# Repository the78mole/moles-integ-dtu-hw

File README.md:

# Moles Integration DTU Hardware

This is a specialized integration module that combines an ESP32 microcontroller with a sub-GHz transceiver, primarily designed as a hardware foundation for [AhoyDTU](https://github.com/lumapu/ahoy/) and [OpenDTU](https://github.com/tbnobody/OpenDTU) solar inverter monitoring systems.

## Table of Contents

- [Features](#features)
- [Hardware Specifications](#hardware-specifications)
- [Hardware Assembly](#hardware-assembly)
- [Pin Mapping](#pin-mapping)
- [Software Installation](#software-installation)
- [Configuration](#configuration)
- [Troubleshooting](#troubleshooting)
- [Performance Specifications](#performance-specifications)
- [Improvements](#improvements)
- [Contributing](#contributing)
- [License](#license)
- [Resources](#resources)

## Features

- **ESP32 Integration**: Full ESP32 development board compatibility
- **Sub-GHz Communication**: NRF24L01+ transceiver support for solar inverter communication
- **Compact Design**: Optimized PCB layout for minimal footprint
- **Open Source**: Full KiCad project files and documentation
- **DTU Ready**: Pre-configured for AhoyDTU and OpenDTU deployment
- **RF Performance**: Optimized RF design with optional PA+LNA enhancement
- **Easy Assembly**: Interactive BOM and detailed assembly instructions

## Hardware Specifications

### Core Components

| Component | Specification | Description |
|-----------|--------------|-------------|
| **Microcontroller** | ESP32-WROOM-32 | Dual-core Xtensa LX6, WiFi & Bluetooth |
| **RF Transceiver** | NRF24L01+ | 2.4GHz ISM band, up to 2Mbps |
| **Power Supply** | 3.3V/5V compatible | On-board voltage regulation |
| **Flash Memory** | 4-16MB (ESP32 internal) | Program and data storage, depending on chosen WROOM-Module |
| **RAM** | 520KB (ESP32 internal) | SRAM for program execution |

### Physical Specifications

- **PCB Dimensions**: ~70mm x 50mm (approximate)
- **Layer Count**: 2-layer PCB
- **Operating Temperature**: -40°C to +85°C
- **Power Consumption**: 
  - Active: ~160mA @ 3.3V
  - Deep Sleep: <10µA
  - WiFi TX: ~200mA peak

### Electrical Specifications

- **Input Voltage**: 3.3V - 5V DC
- **I/O Voltage**: 3.3V logic level
- **Current Rating**: Max 1A total
- **ESD Protection**: Integrated on critical pins

## Hardware Assembly

### Required Tools

- Soldering iron (temperature controlled, 350-400°C)
- Solder (60/40 or lead-free 0.6-0.8mm)
- Flux
- Tweezers
- Magnifying glass or microscope
- Multimeter
- Hot air station (optional, for SMD components)

### Bill of Materials

For a complete and up-to-date bill of materials, please refer to the [Interactive BOM](https://htmlpreview.github.io/?https://github.com/the78mole/moles-integ-dtu-hw/blob/main/docs/ibom.html) which provides:

- Complete component list with values and package sizes
- Component placement visualization
- Interactive component highlighting
- Supplier information and part numbers

### Assembly Instructions

1. **Preparation**
   - Download and print the [PCB documentation](docs/Moles-Integ-DTU-HW.pdf)
   - Gather all components per the BOM
   - Prepare your workspace with proper lighting and ventilation

2. **SMD Component Assembly**
   - Start with the smallest components (resistors, capacitors)
   - Use flux liberally for better solder flow
   - Work from inside-out to avoid shadowing larger components
   - Double-check component orientations, especially for ICs

3. **Through-Hole Components**
   - Install connectors and larger components
   - Ensure proper mechanical fit before soldering
   - Clean flux residue with isopropyl alcohol

4. **ESP32 Module Installation**
   - Align the ESP32-WROOM-32 module carefully
   - Solder all pads ensuring good electrical contact
   - Verify no shorts between adjacent pins

5. **NRF24L01+ Socket/Module**
   - Install either the socket for removable modules or solder the NRF24L01+ directly
   - Verify pin alignment matches the board silkscreen
   - Test continuity of critical connections (VCC, GND, SPI pins)

6. **Quality Control**
   - Visual inspection for solder bridges
   - Continuity testing of power rails
   - Check for correct component placement

### Assembly Verification

Before first power-up:

```bash
# Basic continuity checks
- VCC to GND: Should be open (high resistance)
- 3.3V rail continuity
- SPI bus connectivity (MOSI, MISO, SCK, CS)
- ESP32 programming pins accessibility
```

## Pin Mapping

### ESP32 to NRF24L01+ Connections

| ESP32 Pin | Function | NRF24L01+ Pin | Description |
|-----------|----------|---------------|-------------|
| GPIO18 | SPI_SCK | SCK | SPI Clock |
| GPIO23 | SPI_MOSI | MOSI | SPI Master Out |
| GPIO19 | SPI_MISO | MISO | SPI Master In |
| GPIO5 | SPI_CS | CSN | SPI Chip Select |
| GPIO4 | GPIO | CE | Chip Enable |
| GPIO2 | GPIO | IRQ | Interrupt Request |
| 3V3 | Power | VCC | 3.3V Power Supply |
| GND | Ground | GND | Ground |

### Additional GPIO Mapping

| ESP32 Pin | Function | Description |
|-----------|----------|-------------|
| GPIO0 | BOOT | Boot mode selection |
| GPIO2 | LED | Status LED (if populated) |
| EN | Reset | External reset input |
| GPIO1 | UART_TX | Serial transmit |
| GPIO3 | UART_RX | Serial receive |

## Software Installation

### Prerequisites

- **ESP-IDF**: Version 4.4+ or Arduino IDE with ESP32 support
- **PlatformIO**: Recommended for advanced development
- **Git**: For cloning repositories
- **USB-to-Serial Driver**: CP210x or CH340 depending on your board

### Installing OpenDTU

OpenDTU is the recommended firmware for this hardware platform.

1. **Clone the Repository**
   ```bash
   git clone https://github.com/tbnobody/OpenDTU.git
   cd OpenDTU
   ```

2. **Configure PlatformIO**
   ```bash
   # Install PlatformIO if not already installed
   pip install platformio
   
   # Build the project
   pio run -e generic_esp32
   ```

3. **Flash the Firmware**
   ```bash
   # Connect the board via USB
   # Put ESP32 in programming mode (hold BOOT, press RESET, release BOOT)
   pio run -e generic_esp32 -t upload
   ```

### Installing AhoyDTU

Alternative firmware option with different feature set.

1. **Clone and Build**
   ```bash
   git clone https://github.com/lumapu/ahoy.git
   cd ahoy
   pio run -e esp32-wroom32-devkit
   ```

2. **Configuration**
   - Edit `config.h` for your specific inverter setup
   - Configure WiFi credentials
   - Set up MQTT broker details

### First Boot Configuration

1. **WiFi Setup**
   - Connect to the ESP32 access point (typically "OpenDTU-XXXX")
   - Navigate to the web interface
   - Configure your WiFi network credentials

2. **Inverter Configuration**
   - Enter your inverter serial numbers
   - Configure communication parameters
   - Set up monitoring intervals

## Configuration

### Web Interface

After successful installation, access the web interface:

- **Default IP**: Check your router's DHCP table or use mDNS
- **Default URL**: `http://opendtu.local` or `http://[IP_ADDRESS]`
- **Default Credentials**: Usually no authentication required initially

### Key Configuration Parameters

```yaml
# WiFi Configuration
wifi:
  ssid: "YourNetworkName"
  password: "YourNetworkPassword"
  
# MQTT Configuration
mqtt:
  broker: "192.168.1.100"
  port: 1883
  topic_prefix: "solar"
  
# Inverter Configuration
inverters:
  - serial: 1234567890
    name: "Inverter 1"
    type: "HM-600"
```

### Performance Tuning

For optimal RF performance:

1. **Antenna Placement**
   - Keep antenna away from metal objects
   - Ensure clear line of sight to inverters
   - Consider external antenna for better range

2. **Power Management**
   - Configure deep sleep modes for battery operation
   - Optimize polling intervals
   - Use efficient data transmission protocols

## Troubleshooting

### Common Issues

#### No WiFi Connection
```bash
# Check if ESP32 is in AP mode
# Look for "OpenDTU-XXXX" or "AhoyDTU-XXXX" network
# Connect and configure via web interface
```

#### RF Communication Problems
1. **Check NRF24L01+ Module**
   - Verify power supply (3.3V)
   - Check SPI connections
   - Ensure proper antenna connection

2. **Inverter Communication**
   - Verify inverter serial numbers
   - Check RF channel configuration
   - Monitor signal strength indicators

#### Programming Issues
```bash
# Put ESP32 in programming mode
# Hold BOOT button while pressing RESET
# Release RESET, then release BOOT
# Attempt upload again
```

### Diagnostic Commands

```bash
# Monitor serial output
pio device monitor -b 115200

# Check memory usage
pio run -t size

# Clean build artifacts
pio run -t clean
```

### Debug Output

Enable debug logging in your firmware configuration:

```cpp
// In Arduino IDE or PlatformIO
#define DEBUG_LEVEL ARDUHAL_LOG_LEVEL_DEBUG
```

## Performance Specifications

### RF Performance

| Parameter | Typical Value | Maximum Value | Unit |
|-----------|---------------|---------------|------|
| **Transmit Power** | 0 | +4 | dBm |
| **Receive Sensitivity** | -85 | -90 | dBm |
| **Range (Line of Sight)** | 100 | 200 | meters |
| **Range (Indoor)** | 20 | 50 | meters |
| **Data Rate** | 250k | 2M | bps |

### Power Consumption

| Mode | Current | Duration | Notes |
|------|---------|----------|-------|
| **Active WiFi** | 160mA | Continuous | Normal operation |
| **RF TX Peak** | 200mA | <1ms | During transmission |
| **Light Sleep** | 15mA | Variable | WiFi maintained |
| **Deep Sleep** | <10µA | Hours | Wake on timer/GPIO |

### Environmental Specifications

- **Operating Temperature**: -40°C to +85°C
- **Storage Temperature**: -65°C to +125°C
- **Humidity**: 5% to 95% RH (non-condensing)
- **Altitude**: Up to 3000m above sea level

## Improvements

### Hardware Enhancements

#### PA+LNA RF Frontend

To significantly improve RF performance and range:

**Benefits:**
- Increased transmit power (+20dBm typical)
- Improved receiver sensitivity (-100dBm)
- Extended range (up to 1km line of sight)

**Implementation:**
1. **Hardware Modification**
   - Add RFX2401C or similar PA+LNA module
   - Modify RF trace routing
   - Add antenna switching control

2. **Parts Required**
   - RFX2401C PA+LNA module
   - Additional control GPIOs
   - Modified PCB or breakout board

3. **Assembly Guide**
   - Follow the detailed guide: [NRF24L01+PA+LNA Module Build](https://www.instructables.com/How-to-Build-Your-Own-NRF24L01palna-Module/)
   - Ensure proper shielding and ground plane
   - Test RF performance with spectrum analyzer

#### Alternative Power Options

1. **Battery Operation**
   - Add LiPo battery connector
   - Implement charging circuit
   - Power management optimization

2. **PoE Support**
   - Add IEEE 802.3af PoE module
   - Galvanic isolation
   - Surge protection

#### Future Hardware Revisions

- **USB-C Connector**: Modern connector standard
- **On-board Antenna**: Integrated PCB antenna option
- **Status LEDs**: Visual feedback for operation modes
- **External Antenna Connector**: U.FL or SMA connector
- **Environmental Sensors**: Temperature, humidity monitoring

### Software Enhancements

#### Advanced Features
- **OTA Updates**: Over-the-air firmware updates
- **Data Logging**: Local storage of historical data
- **Advanced Scheduling**: Complex polling schedules
- **Multi-Protocol Support**: Support for additional inverter protocols

#### Integration Options
- **Home Assistant**: Native integration
- **InfluxDB**: Time-series database support
- **Grafana**: Advanced visualization
- **Node-RED**: Visual programming interface

## Contributing

We welcome contributions to improve this project! Here's how you can help:

### Development Workflow

1. **Fork the Repository**
   ```bash
   git clone https://github.com/[your-username]/moles-integ-dtu-hw.git
   cd moles-integ-dtu-hw
   ```

2. **Create Feature Branch**
   ```bash
   git checkout -b feature/your-improvement
   ```

3. **Make Changes**
   - Follow KiCad design rules
   - Update documentation
   - Test thoroughly

4. **Submit Pull Request**
   - Provide clear description
   - Include test results
   - Reference related issues

### Design Guidelines

#### Hardware Design
- **KiCad Version**: Use latest stable version
- **Design Rules**: Follow IPC standards
- **Component Selection**: Prefer widely available parts
- **Documentation**: Update schematic and PCB documentation

#### Documentation
- **Markdown Format**: Use standard markdown
- **Images**: Optimize file sizes, use PNG/JPG
- **Links**: Verify all external links
- **Accuracy**: Test all instructions

### Bug Reports

When reporting bugs, please include:

- **Hardware Version**: PCB revision and component details
- **Software Version**: Firmware version and configuration
- **Environment**: Operating conditions and setup
- **Reproduction Steps**: Clear steps to reproduce the issue
- **Expected vs Actual**: What should happen vs what actually happens

### Feature Requests

For new features:

- **Use Case**: Describe the problem you're trying to solve
- **Proposed Solution**: Your suggested approach
- **Alternatives**: Other solutions you've considered
- **Impact**: Who would benefit from this feature

## License

This project is licensed under the [TAPR Open Hardware License](LICENSE). This means:

### You are free to:
- **Study** the design and understand how it works
- **Modify** the design for your own purposes
- **Distribute** copies of the design
- **Distribute** modified versions of the design

### Under the following conditions:
- **Attribution**: Credit the original designers
- **Share Alike**: Distribute modifications under the same license
- **Documentation**: Provide design files in open formats
- **Notice**: Include license notices in distributions

### Commercial Use
Commercial use is permitted under the TAPR OHL, but please review the full license terms for specific requirements regarding documentation and attribution.

## Resources

### Official Documentation
- **Schematics**: [PDF Documentation](docs/Moles-Integ-DTU-HW.pdf)
- **Interactive BOM**: [iBOM Tool](https://htmlpreview.github.io/?https://github.com/the78mole/moles-integ-dtu-hw/blob/main/docs/ibom.html)
- **Production Workflow**: [Automated Production Files](docs/PRODUCTION_WORKFLOW.md)
- **Versioning & CI/CD**: [Semantic Versioning and Workflows](docs/VERSIONING_AND_CI.md)
- **KiCad Files**: Complete project files in repository

### Related Projects
- **OpenDTU**: [Advanced DTU firmware](https://github.com/tbnobody/OpenDTU)
- **AhoyDTU**: [Alternative DTU firmware](https://github.com/lumapu/ahoy/)
- **ESP32 Documentation**: [Official ESP32 docs](https://docs.espressif.com/projects/esp-idf/en/latest/)
- **NRF24L01+**: [Datasheet and examples](https://www.nordicsemi.com/products/nrf24l01)

### Community Resources
- **Solar Inverter Monitoring**: [Community forums and guides](https://forum.fhem.de)
- **ESP32 Community**: [ESP32 developer resources](https://esp32.com/)
- **KiCad Community**: [PCB design resources](https://kicad.org/community/)

### Supplier Information
- **PCB Manufacturing**: Recommended suppliers for small batch production
- **Component Sourcing**: Parts availability and alternative components
- **Assembly Services**: Professional assembly options

### Development Tools
- **KiCad**: [Free PCB design software](https://kicad.org/)
- **PlatformIO**: [Advanced embedded development](https://platformio.org/)
- **ESP-IDF**: [ESP32 development framework](https://github.com/espressif/esp-idf)
- **Git**: [Version control system](https://git-scm.com/)

---

**Disclaimer**: This project involves working with electrical circuits and RF equipment. Always follow proper safety procedures and local regulations. The authors are not responsible for any damage or injury resulting from the use of this design.

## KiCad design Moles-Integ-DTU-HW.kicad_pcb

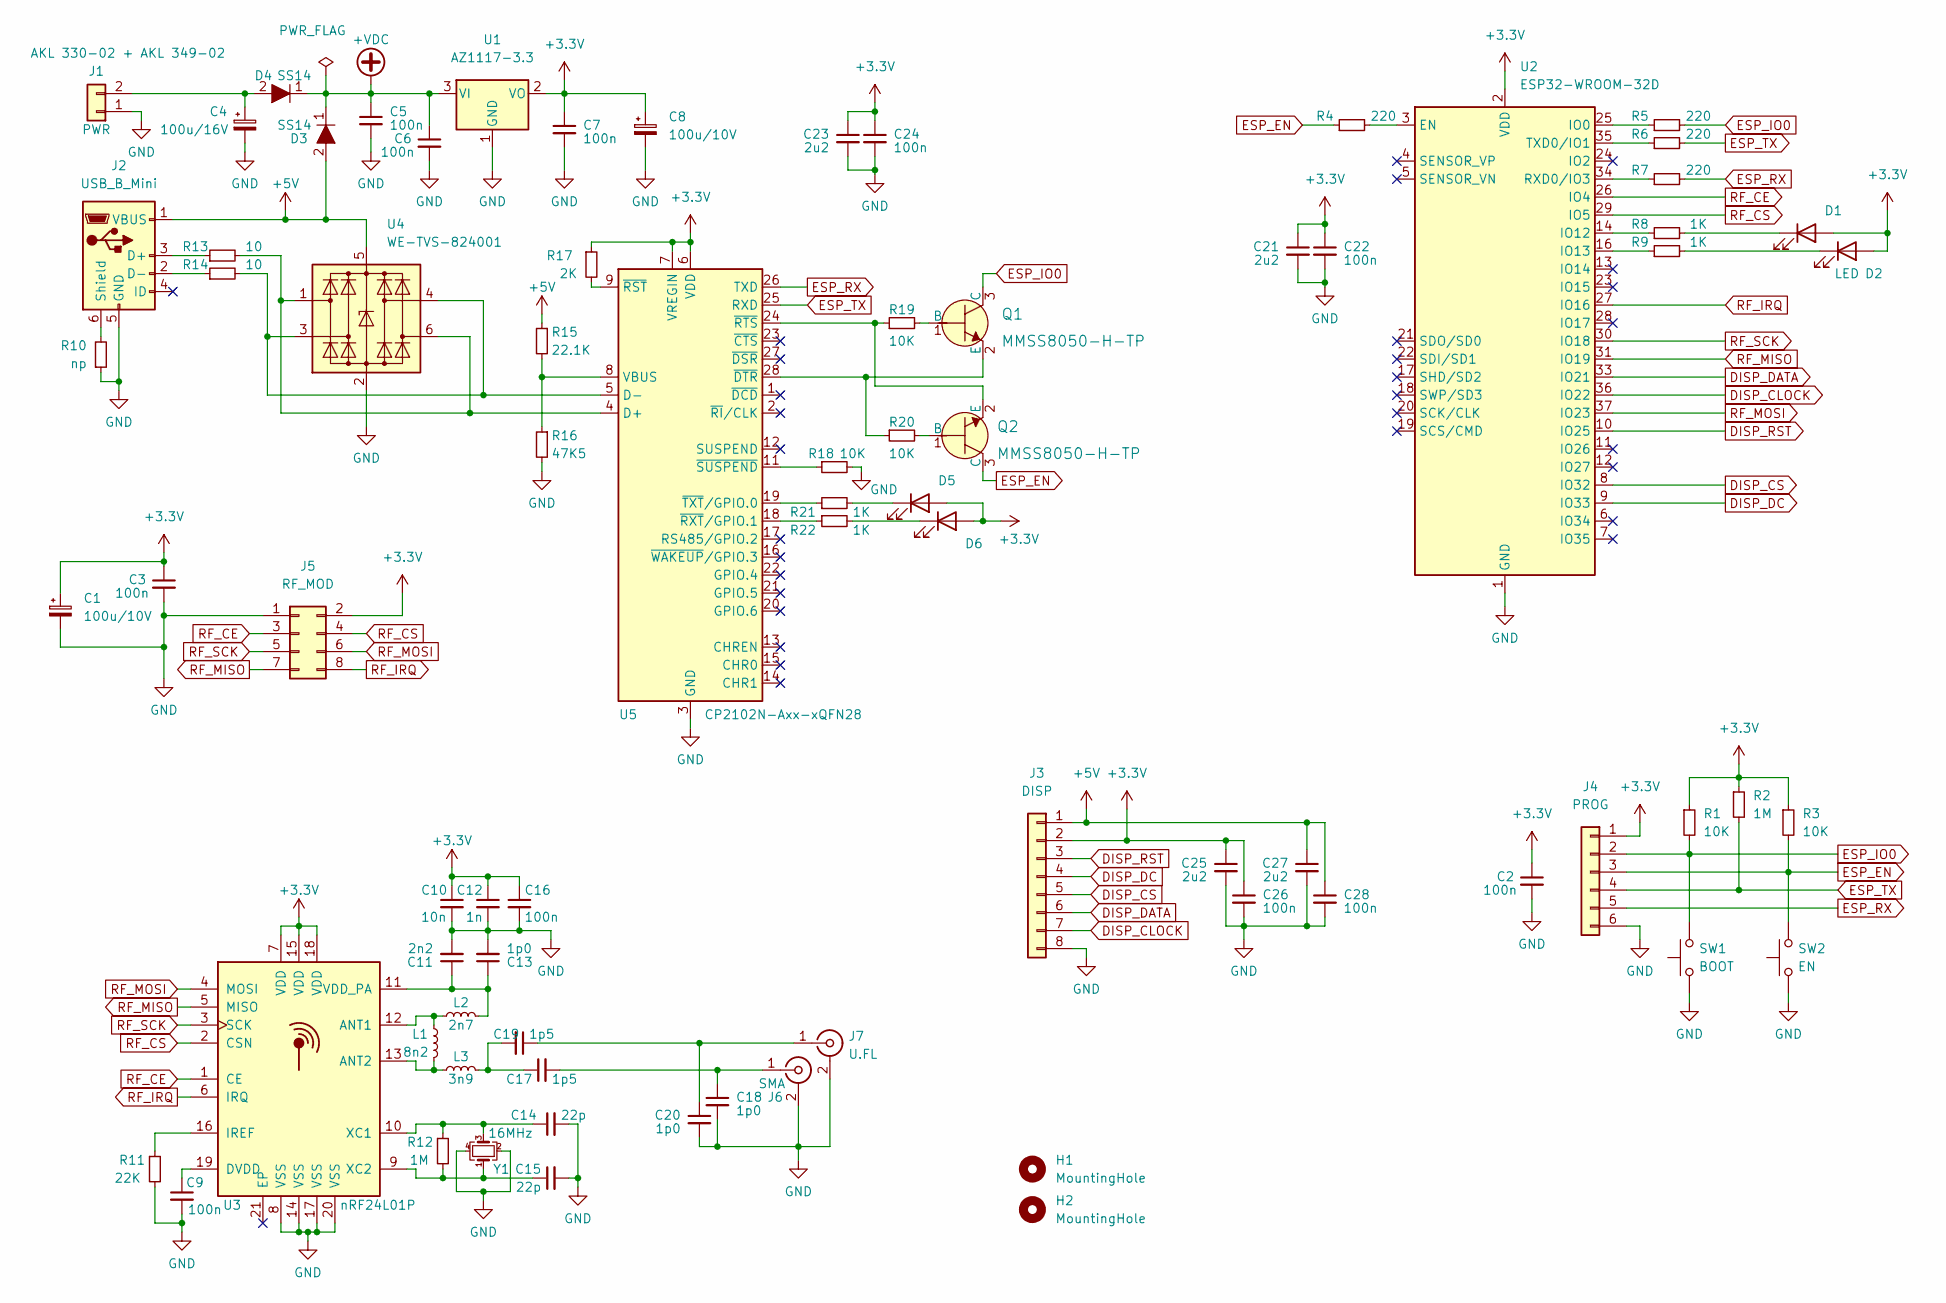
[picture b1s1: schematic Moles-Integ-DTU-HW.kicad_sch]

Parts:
C1, C8: 100u/10V; C_Radial_D6.3mm_H11.0mm_P2.50mm
C2, C3, C5, C6, C7, C9, C16, C22, C24, C26, C28: 100n; C_0603_1608Metric_Pad1.08x0.95mm_HandSolder
C4: 100u/16V; C_Radial_D6.3mm_H11.0mm_P2.50mm
C10: 10n; C_0603_1608Metric_Pad1.08x0.95mm_HandSolder
C11: 2n2; C_0402_1005Metric_Pad0.74x0.62mm_HandSolder
C12: 1n; C_0603_1608Metric_Pad1.08x0.95mm_HandSolder
C13, C18, C20: 1p0; C_0402_1005Metric_Pad0.74x0.62mm_HandSolder
C14, C15: 22p; C_0402_1005Metric_Pad0.74x0.62mm_HandSolder
C17, C19: 1p5; C_0402_1005Metric_Pad0.74x0.62mm_HandSolder
C21, C23, C25, C27: 2u2; C_0603_1608Metric_Pad1.08x0.95mm_HandSolder
D1, D5, D6: (no value)
D2: LED; LED_0603_1608Metric_Pad1.05x0.95mm_HandSolder
D3, D4: SS14; D_SMA-SMB_Universal_Handsoldering; MPN SS14; Digi-Key_PN SS14CT-ND
H1, H2: MountingHole; MountingHole_4.3mm_M4_DIN965
J1: PWR; TerminalBlock_RND_205-00001_1x02_P5.00mm_Horizontal
J2: USB_B_Mini; USB_Mini-B_Wuerth_65100516121_Horizontal
J3: DISP; IDC-Header_2x04_P2.54mm_Vertical
J4: PROG; PinHeader_2x03_P2.54mm_Vertical
J5: RF_MOD; PinSocket_2x04_P2.54mm_Vertical
J6: SMA; SMA_Amphenol_901-143_Horizontal
J7: U.FL; U.FL_Hirose_U.FL-R-SMT-1_Vertical; MPN U.FL-R-SMT-1(10)
L1: 8n2; L_0402_1005Metric_Pad0.77x0.64mm_HandSolder
L2: 2n7; L_0402_1005Metric_Pad0.77x0.64mm_HandSolder
L3: 3n9; L_0402_1005Metric_Pad0.77x0.64mm_HandSolder
Q1, Q2: MMSS8050-H-TP; SOT-23; MPN MMSS8050-H-TP; Digi-Key_PN MMSS8050-H-TPMSCT-ND
R1, R3, R18, R19, R20: 10K; R_0603_1608Metric_Pad0.98x0.95mm_HandSolder
R2, R12: 1M; R_0603_1608Metric_Pad0.98x0.95mm_HandSolder
R4, R5, R6, R7: 220; R_0603_1608Metric_Pad0.98x0.95mm_HandSolder
R8, R9, R21, R22: 1K; R_0603_1608Metric_Pad0.98x0.95mm_HandSolder
R10: np; R_0603_1608Metric_Pad0.98x0.95mm_HandSolder
R11: 22K; R_0603_1608Metric_Pad0.98x0.95mm_HandSolder
R13, R14: 10; R_0603_1608Metric_Pad0.98x0.95mm_HandSolder
R15: 22.1K; R_0603_1608Metric_Pad0.98x0.95mm_HandSolder
R16: 47K5; R_0603_1608Metric_Pad0.98x0.95mm_HandSolder
R17: 2K; R_0603_1608Metric_Pad0.98x0.95mm_HandSolder
SW1: BOOT; SW_SPST_B3SL-1002P
SW2: EN; SW_SPST_B3SL-1002P
U1: AZ1117-3.3; SOT-223-3_TabPin2
U2: ESP32-WROOM-32D; ESP32-WROOM-32
U3: nRF24L01P; QFN-20-1EP_4x4mm_P0.5mm_EP2.5x2.5mm
U4: WE-TVS-824001; SOT-23-6
U5: CP2102N-Axx-xQFN28; QFN-28-1EP_5x5mm_P0.5mm_EP3.35x3.35mm
Y1: 16MHz; Crystal_SMD_3225-4Pin_3.2x2.5mm_HandSoldering

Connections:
+3V3: C1.1, C2.1, C3.1, C7.1, C8.1, C10.1, C12.1, C16.1, C21.1, C22.1, C23.1, C24.1, C25.1, C26.1, D1.2 (A), D2.2 (A), D5.2 (A), D6.2 (A), J3.2, J4.1, J5.2, R1.1, R2.1, R3.1, R17.1, U1.2 (VO), U2.2 (VDD), U3.7 (VDD), U3.15 (VDD), U3.18 (VDD), U5.6 (VDD), U5.7 (VREGIN)
+5V: C27.1, C28.1, D4.2, J2.1 (VBUS), J3.1, R15.1, U4.5 (VBUS)
+VDC: C5.1, C6.1, D3.1, D4.1, U1.3 (VI)
DISP_CLOCK: J3.7, U2.36 (IO22)
DISP_CS: J3.5, U2.8 (IO32)
DISP_DATA: J3.6, U2.33 (IO21)
DISP_DC: J3.4, U2.9 (IO33)
DISP_RST: J3.3, U2.10 (IO25)
ESP_EN: J4.3, Q2.3 (C), R3.2, R4.1, SW2.2
ESP_IO0: J4.2, Q1.3 (C), R1.2, R5.2, SW1.2
ESP_RX: J4.5, R7.2, U5.26 (TXD)
ESP_TX: J4.4, R2.2, R6.2, U5.25 (RXD)
GND: C1.2, C2.2, C3.2, C4.2, C5.2, C6.2, C7.2, C8.2, C9.2, C10.2, C11.2, C12.2, C13.2, C14.2, C15.2, C16.2, C18.2, C20.2, C21.2, C22.2, C23.2, C24.2, C25.2, C26.2, C27.2, C28.2, J1.1, J2.5 (GND), J3.8, J4.6, J5.1, J6.2 (Ext), J7.2 (Ext), R10.1, R11.2, R16.2, R18.2, SW1.1, SW2.1, U1.1 (GND), U2.1 (GND), U2.15 (GND), U2.38 (GND), U2.39 (GND), U3.8 (VSS), U3.14 (VSS), U3.17 (VSS), U3.20 (VSS), U4.2 (GND), U5.3 (GND), U5.29 (GND), Y1.2, Y1.4
unnamed: C4.1, D3.2, J1.2
unnamed: C9.1, U3.19 (DVDD)
unnamed: C11.1, C13.1, L2.2, U3.11 (VDD_PA)
unnamed: C14.1, R12.1, U3.10 (XC1), Y1.3
unnamed: C15.1, R12.2, U3.9 (XC2), Y1.1
unnamed: C17.1, C19.2, L3.2
unnamed: C17.2, C18.1, J6.1 (In)
unnamed: C19.1, C20.1, J7.1 (In)
unnamed: D1.1 (K), R8.2
unnamed: D2.1 (K), R9.2
unnamed: D5.1 (K), R21.2
unnamed: D6.1 (K), R22.2
unnamed: J2.2 (D-), R14.1
unnamed: J2.3 (D+), R13.1
unnamed: J2.6 (Shield), R10.2
unnamed: L1.1, L2.1, U3.12 (ANT1)
unnamed: L1.2, L3.1, U3.13 (ANT2)
unnamed: Q1.1 (B), R19.2
unnamed: Q1.2 (E), R20.1, U5.28 (~DTR)
unnamed: Q2.1 (B), R20.2
unnamed: Q2.2 (E), R19.1, U5.24 (~RTS)
unnamed: R4.2, U2.3 (EN)
unnamed: R5.1, U2.25 (IO0)
unnamed: R6.1, U2.35 (TXD0/IO1)
unnamed: R7.1, U2.34 (RXD0/IO3)
unnamed: R8.1, U2.14 (IO12)
unnamed: R9.1, U2.16 (IO13)
unnamed: R11.1, U3.16 (IREF)
unnamed: R13.2, U4.1 (I/O1), U4.6 (I/O4), U5.4 (D+)
unnamed: R14.2, U4.3 (I/O2), U4.4 (I/O3), U5.5 (D-)
unnamed: R15.2, R16.1, U5.8 (VBUS)
unnamed: R17.2, U5.9 (~RST)
unnamed: R18.1, U5.11 (~SUSPEND)
unnamed: R21.1, U5.19 (~TXT/GPIO.0)
unnamed: R22.1, U5.18 (~RXT/GPIO.1)
RF_CE: J5.3, U2.26 (IO4), U3.1 (CE)
RF_CS: J5.4, U2.29 (IO5), U3.2 (CSN)
RF_IRQ: J5.8, U2.27 (IO16), U3.6 (IRQ)
RF_MISO: J5.7, U2.31 (IO19), U3.5 (MISO)
RF_MOSI: J5.6, U2.37 (IO23), U3.4 (MOSI)
RF_SCK: J5.5, U2.30 (IO18), U3.3 (SCK)

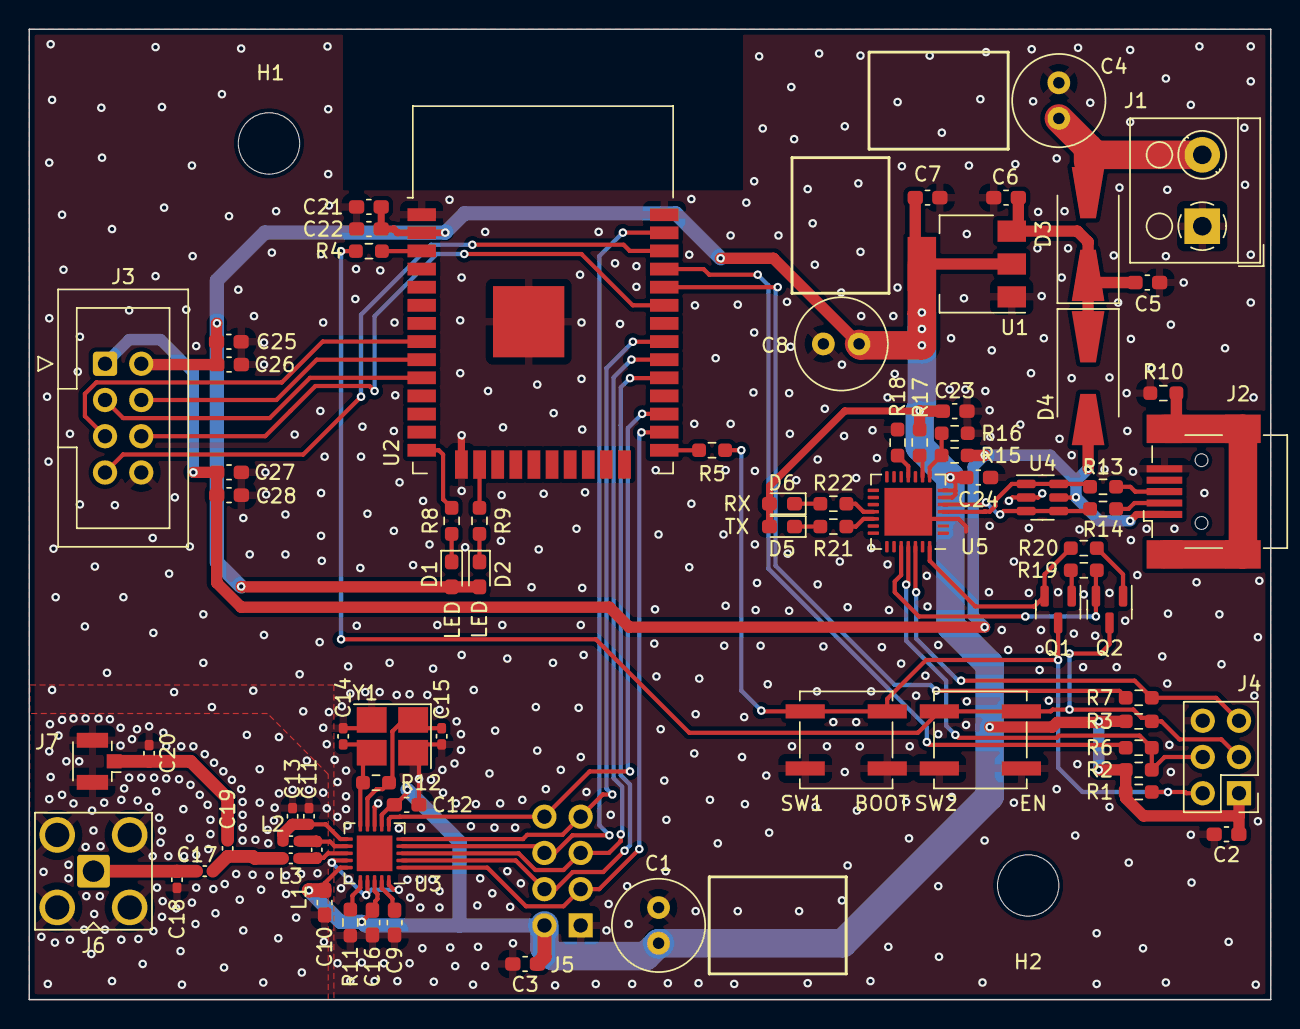
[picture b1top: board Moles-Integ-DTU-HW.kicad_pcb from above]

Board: 2 copper layers, 87.0 x 68.0 mm, 78 parts (1 on the bottom side), 54 nets.

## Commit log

2023-09-12 Initital commit V0.0.1
2023-09-12 Added schematics and iBOM
2023-09-12 Added a link to iBom to README
2023-09-12 Create LICENSE
2023-09-12 Added Text to PCB silkscreen and updated 3D
2023-09-14 Added some improvement section to README
    - Improvement: RF PA/LNA frontend for increased performance
2025-09-10 Initial plan
2025-09-10 Comprehensive extension of README with detailed hardware and software documentation
2025-09-12 Add GitHub templates and fix README flash memory specification
2025-09-12 Add GitHub Actions workflow for automated production file generation
2025-09-12 Add documentation for production workflow
2025-09-12 Add semantic versioning and PR production file check workflows
2025-09-12 Add comprehensive versioning and CI/CD documentation
2025-09-12 Fix corrupted YAML workflow files by removing line numbers
2025-09-12 Add explicit condition to prevent workflow running on incorrect events
2025-09-12 Add debug information to workflow to understand trigger issue
2025-09-12 Replace problematic workflow with simplified production files workflow

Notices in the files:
README.md:
License: TAPR-OHL
